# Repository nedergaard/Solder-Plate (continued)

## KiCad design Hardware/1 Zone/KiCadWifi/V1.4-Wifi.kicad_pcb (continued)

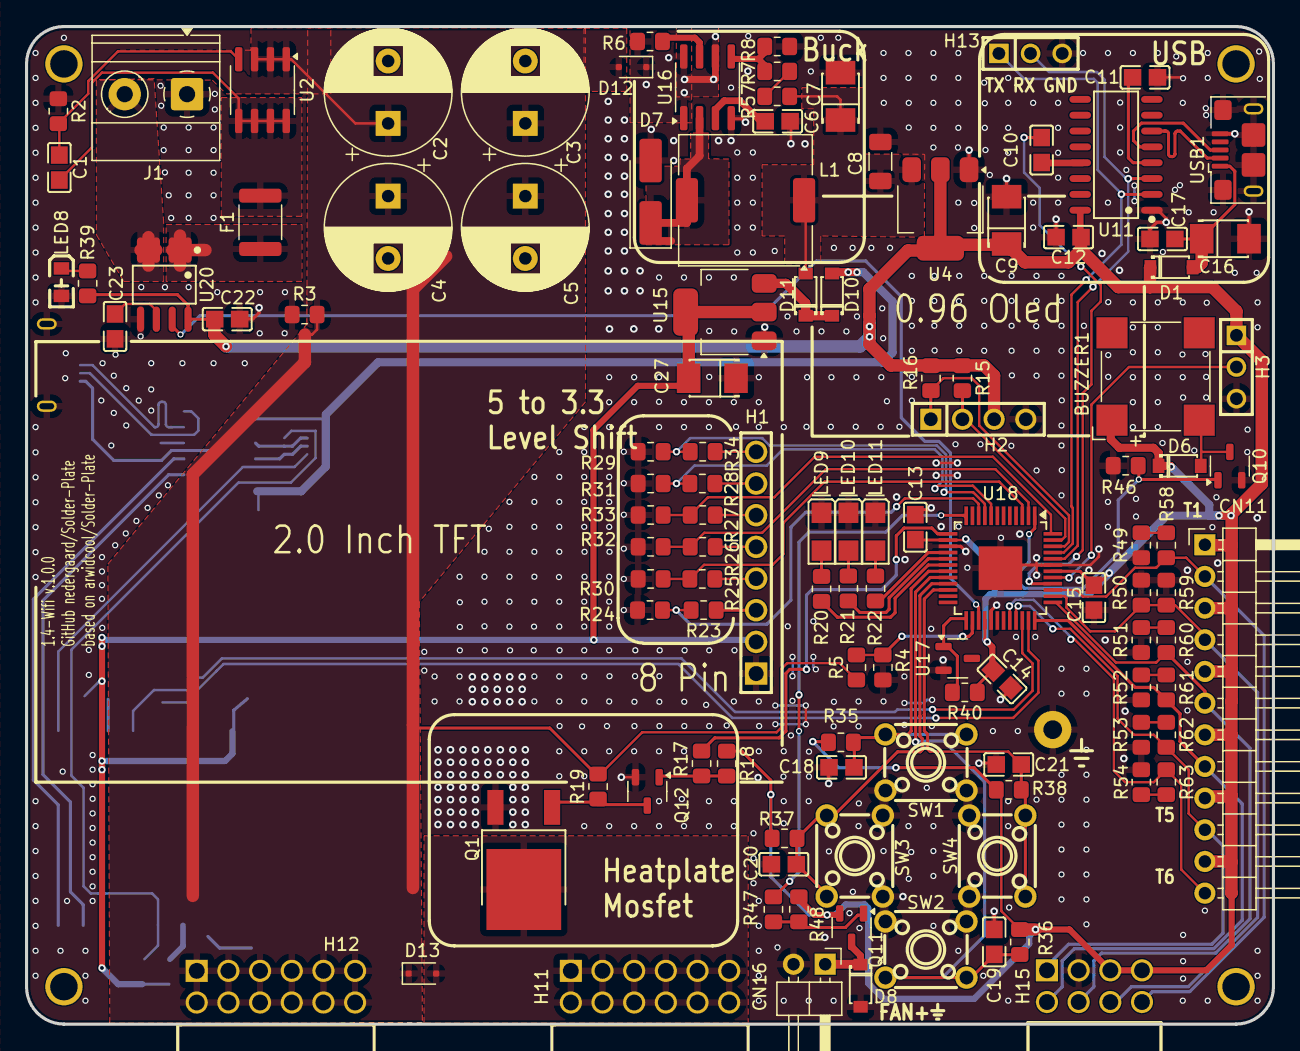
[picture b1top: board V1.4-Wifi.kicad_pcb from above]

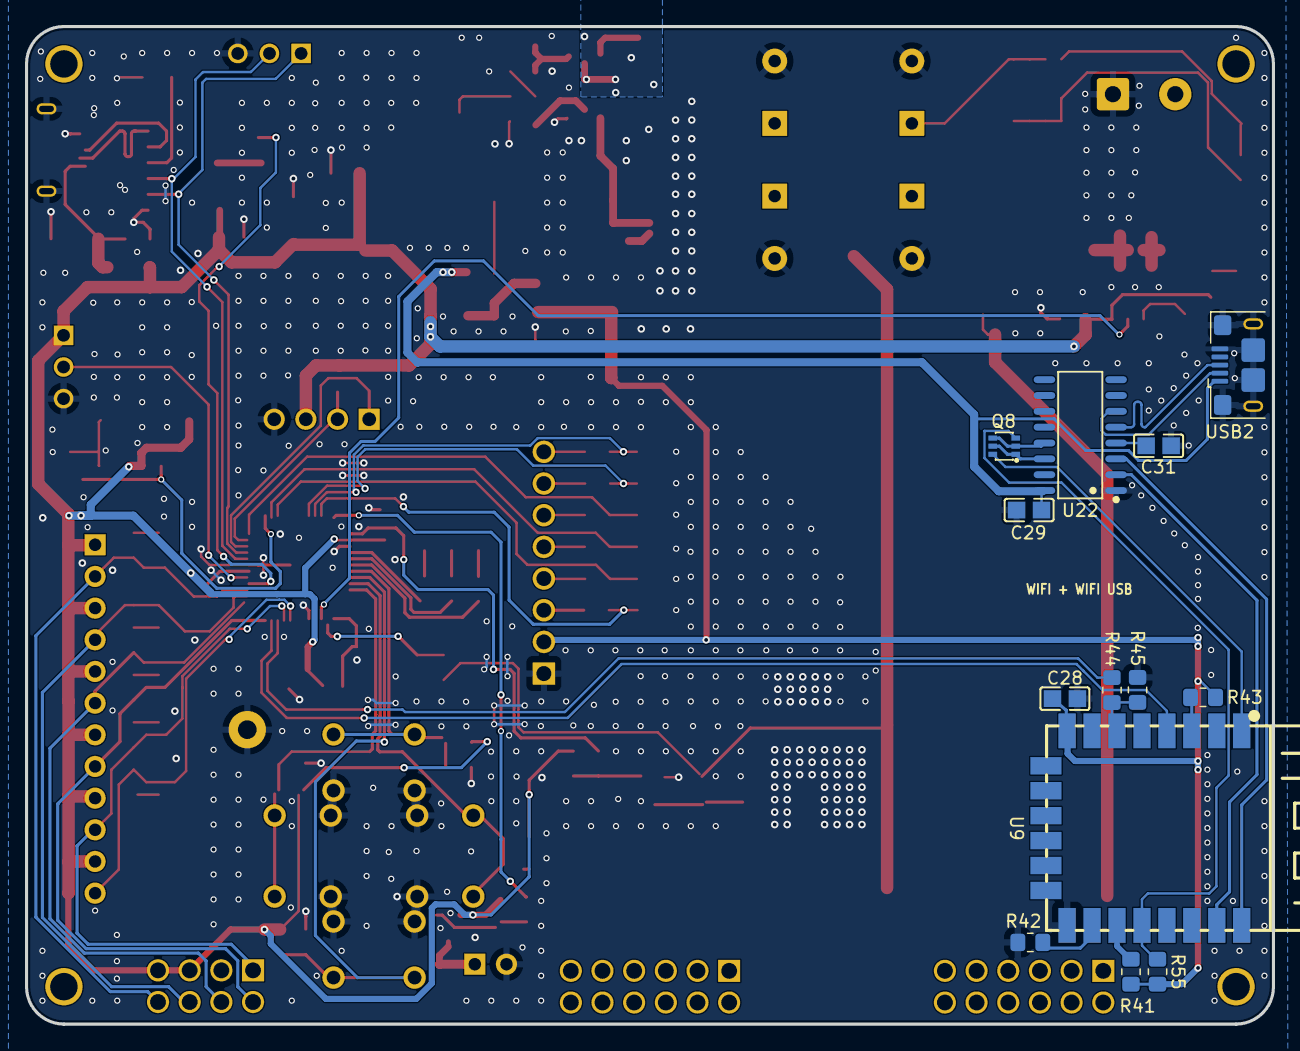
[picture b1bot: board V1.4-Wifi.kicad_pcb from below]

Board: 2 copper layers, 100.0 x 80.0 mm, 128 parts (13 on the bottom side), 90 nets.

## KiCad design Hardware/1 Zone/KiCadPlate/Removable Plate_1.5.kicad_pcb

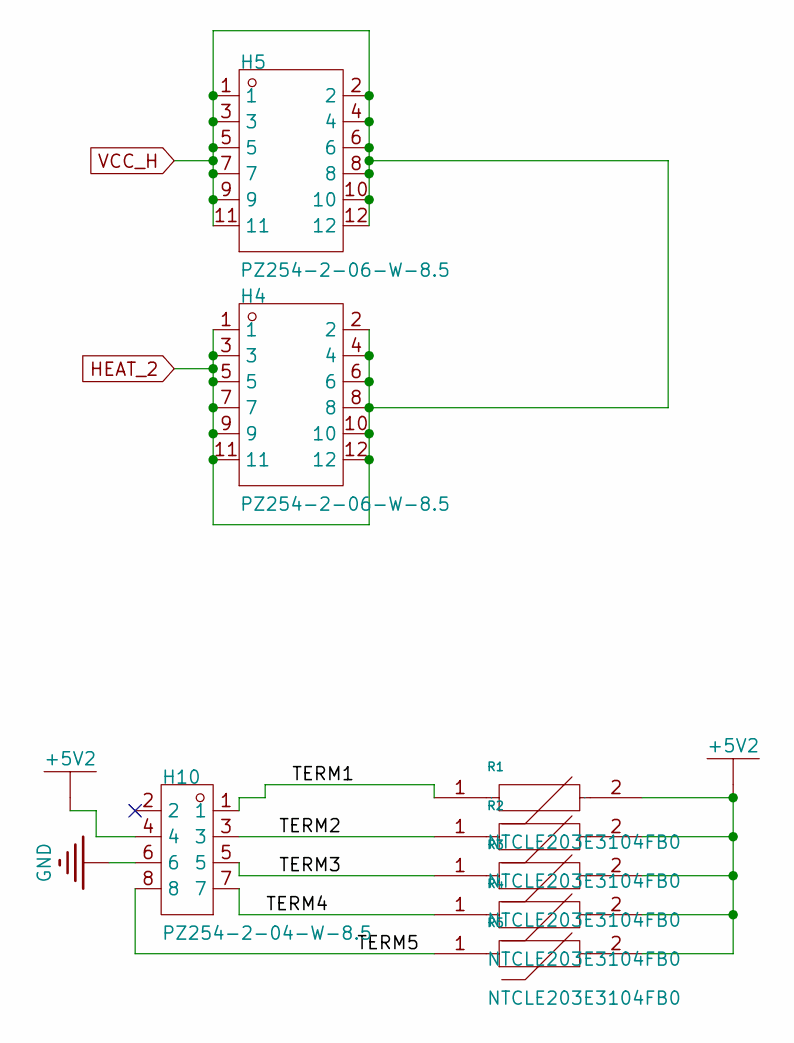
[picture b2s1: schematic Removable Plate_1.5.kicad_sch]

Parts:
H4, H5: PZ254-2-06-W-8.5; HDR-TH_12P-P2.54-H-M-R2-C6-S2.54-N; Manufacturer Part PZ254-2-06-W-8.5; LCSC Part Name 2.54mm2x6P弯插方针
H10: PZ254-2-04-W-8.5; HDR-TH_8P-P2.54-H-M-R2-C4-S2.54-N; Manufacturer Part PZ254-2-04-W-8.5; LCSC Part Name 2.54mm2x4P弯插方针
R1, R2, R3, R4, R5: NTCLE203E3104FB0; PinHeader_1x02_P2.54mm_Vertical; Manufacturer Part NTCLE203E3104FB0; LCSC Part Name 100kΩ电阻精度:±1%

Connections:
+5V2: H10.4, R1.2, R2.2, R3.2, R4.2, R5.2
/TERM1: H10.1, R1.1
/TERM2: H10.3, R2.1
/TERM3: H10.5, R3.1
/TERM4: H10.7, R4.1
/TERM5: H10.8, R5.1
GND: H10.6
HEAT_2: H4.1, H4.2, H4.3, H4.4, H4.5, H4.6, H4.7, H4.8, H4.9, H4.10, H4.11, H4.12, H5.1, H5.2, H5.3, H5.4, H5.5, H5.6, H5.7, H5.8, H5.9, H5.10, H5.11, H5.12

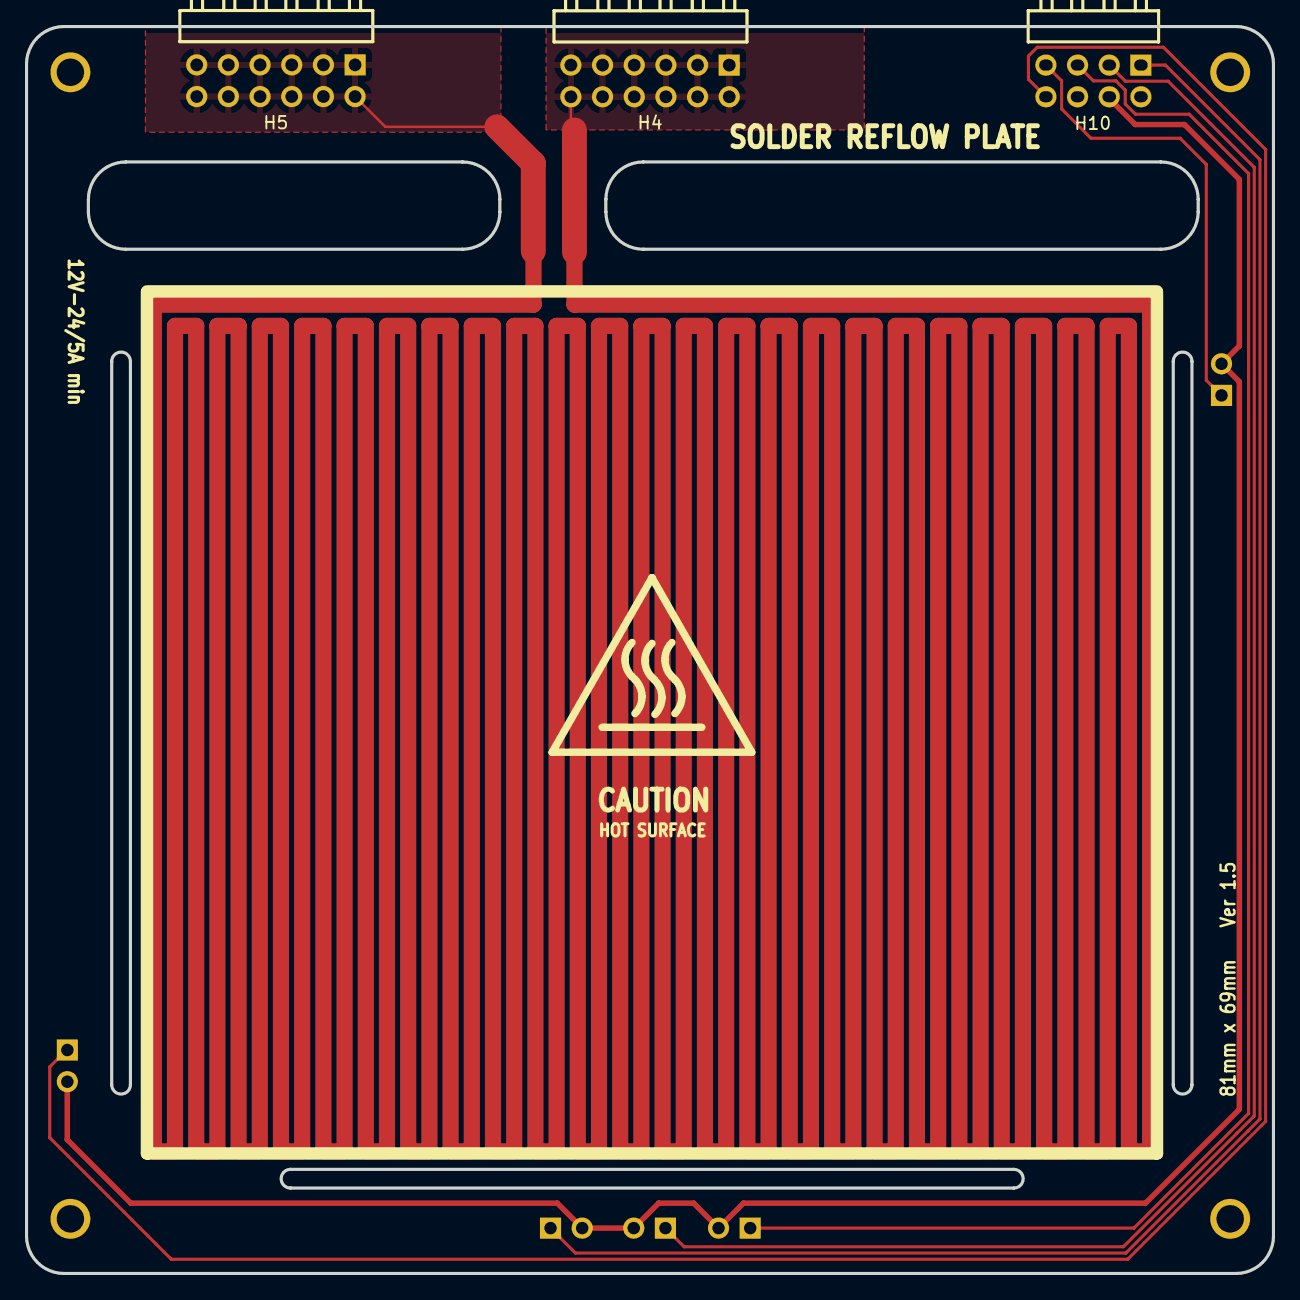
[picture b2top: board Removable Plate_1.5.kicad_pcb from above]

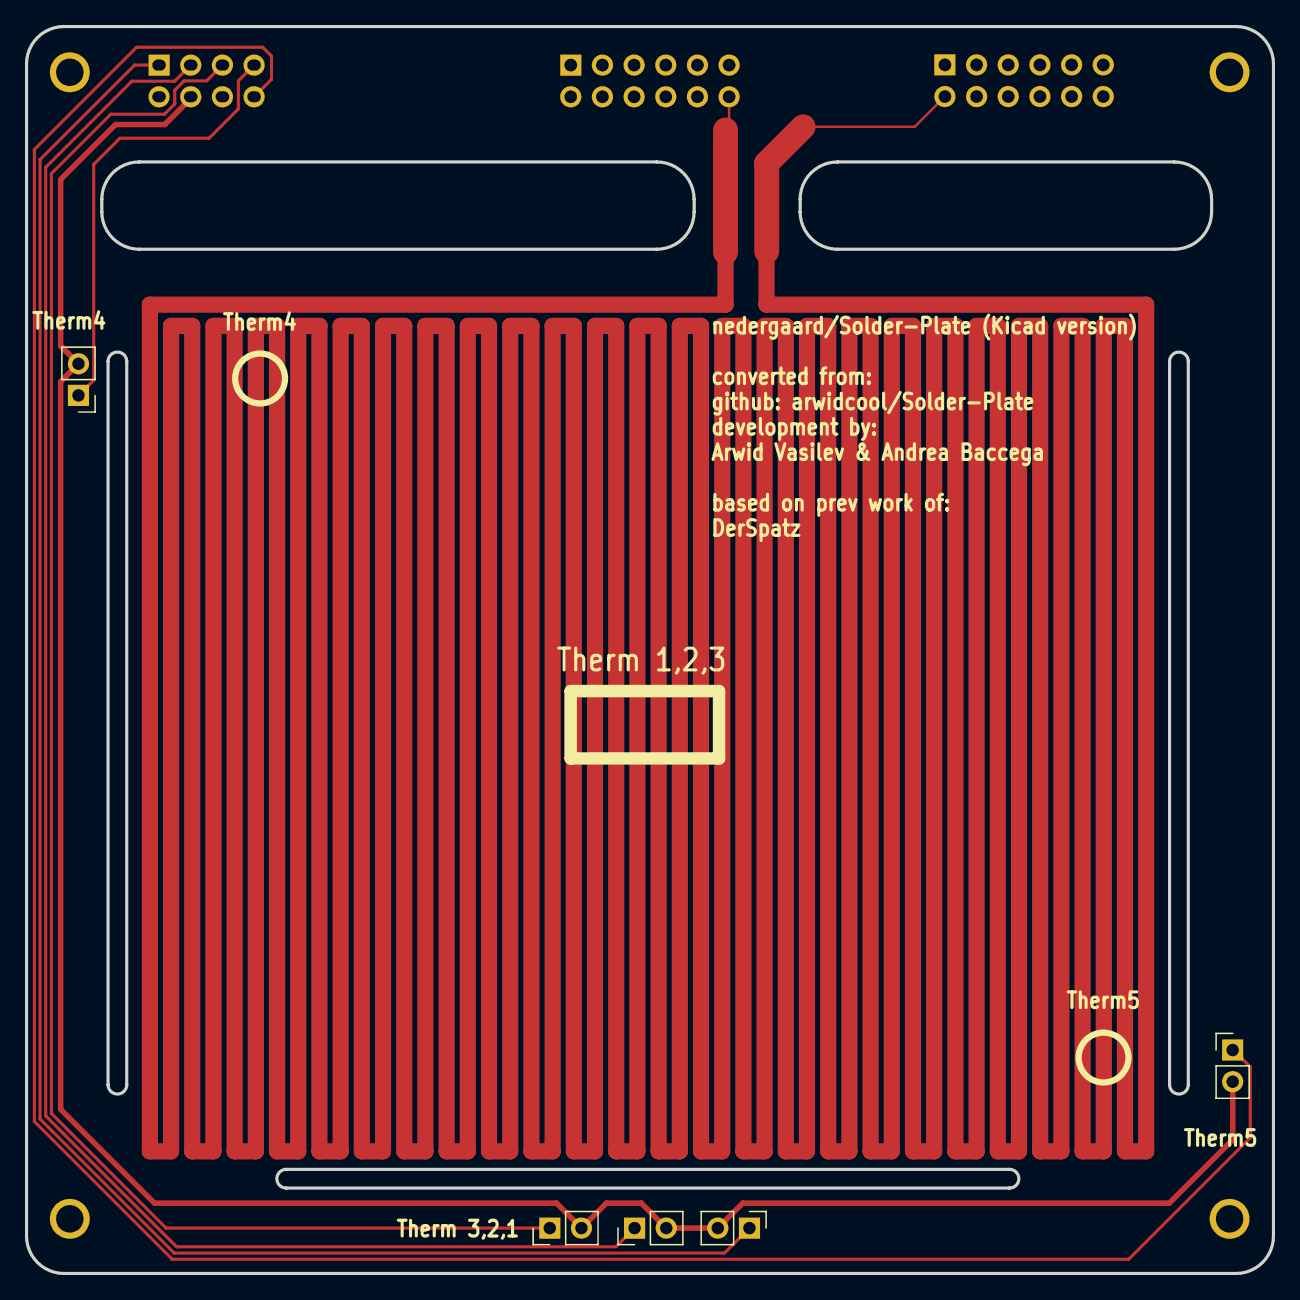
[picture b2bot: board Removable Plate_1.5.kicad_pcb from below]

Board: 2 copper layers, 100.0 x 100.0 mm, 8 parts (5 on the bottom side), 7 nets.

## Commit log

2025-03-30 Added readme note to contribute to the original repo
2025-04-12 Disable conversion of line endings by git
2025-04-12 Git ignore KiCad local files
2025-04-12 Added KiCad 9 project for V1.4-Wifi hardware
2025-04-12 Marked no-connect as such, except 1
2025-04-13 Added custom footprint library
2025-04-13 Replaced part C7, C9, C16 from TC212B107M010B to KEMET T491B107M010AT
2025-04-13 Git ignore KiCad folders with manual backup zips
2025-04-13 Replaced XH2 connectors with pin headers (CN11-CN16). Added Thermistor 1 to connector. Update 5V symbols with +5V value to inform KiCad about net connection.
2025-04-13 Replaced part D1, D6-D8, D10-D11 from MBR0520 to B0520LW-7-F
2025-04-13 Removed unused footprints (C2-C5)
2025-04-13 Updated D12,D13 from B5819 to B5819WSL-TP and updated footprint
2025-04-13 Replaced part F1 from SMD025F-30 to 1812L050/30PR and updated footprint (1812, smaller)
2025-04-13 Replaced part L1 from CDRH74-220MT to VLS6045EX-220M-H and updated footprint. Moved CURRENT_READ trace slightly away from the inductor for noise reasons.
2025-04-14 Replaced part LED8-LED11
2025-04-14 Replaced part Q1 from AOD4184A to IPD90N04S403
2025-04-14 Replaced part Q10 from IRLML2502 to PJA3404A. Updated footprint.
2025-04-14 Replaced part Q11 from SI2300 to PJA3404A to simplify BOM. Updated footprint.
2025-04-14 Replaced part Q12 from S8050 to BC816-16VL. Updated footprint.
2025-04-16 Adjusted resistor value to assist picking correct part by pcb supplier
2025-04-17 Moved C2-C5 back in place
2025-04-17 Fixed R and C values manually looking at EasyEDA editor
2025-04-19 Updated MPN for updated C parts
2025-04-21 Replaced part U2 from AO4409 to DMPH4015SSSQ
2025-04-21 Slighty incresed fill areas connected to U2 for heat dissipation
2025-04-21 Replaced U4 from AMS1117-5.0 to LDI1117-05H
2025-04-21 Replaced U15 from AMS1117-3.3 to LD1117S33CTR
2025-04-27 Upgraded L1 (MSS1048-104MLC) and D7 (SK34SMA-3G). Layout changes to accomodate larger footprints.
2025-04-27 Rotated D7 to shorten GND path. Added VIN fill on bu below U16 for heat dissipation.
2025-04-27 Replaced U17 custom footprint with standard
2025-04-27 Replaced U18 AtMega footprint with center pad. A bit of rerouting and GND stitching for EMC improvements (shrink GND loops)
2025-04-28 Replaced USB1, USB2 to 10118193-0001LF
2025-04-28 Replace Buzzer1 with CMT-8504-100-SMT-TR
2025-04-28 Cleaned pup symbol table
2025-04-28 Reroute (minor), moved via and silkscreen apart, in USB area
2025-04-28 Changed R1,R2 and all 10K resistors to 0805. Fixed comment for C28.
2025-04-28 Changed all 4K7 resistors to 0805.
2025-04-28 Changed all 1K resistors to 0805. Moved R39 and LED8 a little.
2025-04-28 Changed R6-R8,R40-R44,R50,R55 to 0805. Rerouted E_RESET,ESP_BOOT,3.3V. Fixed value of R39,R44
2025-04-29 Changed R45,R47,R49-R54 to 0805. Updated value for R41,R55.
2025-04-29 Changed via drill to 0.300mm. Default net clearance to 0.1mm. Border to edge 0.3mm. Fixed PCB DRC errors. 2 ignored.
2025-04-29 Removed bom field MPN. Renamed Manufacturer Part to mpn.
2025-04-29 Updated R50 to 2K, R6 to 0.33.
2025-04-29 Changed R20,22,39 based on LED calculations
2025-04-29 Changed C8 to 1205
2025-04-30 Added R56 (4K7) and changed R3 to 4K7, to dissipate power safely (slower discharge of caps).
2025-04-30 Added R57, changed R7,R8 to make ref voltage divider use E12. Fixed text with formula for Vout in 7.5V Step Down Converter.
2025-04-30 Removed R9-R14 pots for thermistor. Added R58-R63 to get good resistor matches for recommended values.
2025-04-30 Changed R44 to 2K2, R45 to 3K3 to get a safe conversion from 5V to 3V3 logic (ATMEGA to ESP12)
2025-04-30 Filled values for various header parts
2025-05-05 Replaced C2-C5 and LED10 (+R21) due to availability.
2025-05-10 Tidied up schematics
2025-05-10 Replaced Power Jack with screw terminals. Repurposed R3 to bleeder resistor. R1, R53 removed.
2025-05-17 Renamed MOSTFET to GATE_PIN, to align better with schematics.
2025-05-17 Rerouting for tighter return paths for MOSI and SCK. Moved R4,R5 to avoid cutting return path. Renamed LCD_RST, CD, DC to TFT_RST, TFT_CS, TFT_CS to better align with code.
2025-05-17 Removed H10 7pin header for TFT, for EMC reasons.
2025-05-17 UDPI net shortened and added tight return path.
2025-05-18 I2C_SCL, I2C_SDA return paths tightened
2025-05-18 RXD, TXD return paths tightened
2025-05-18 MEGA_TX, MEGA_RX return paths tightened up
2025-05-20 GATE, FAN_CTRL return paths tightened
2025-05-20 Renamed TFT_LED, TFT_SI_OUT, TFT_SCK_OUT to LCD_* for consistency
2025-05-20 E_TX, R_TX return paths tightened
2025-05-21 Cleaning. Simplified segmented traces.
2025-05-24 Moved D8 for EMC reasons. Refactored Fan ctrl schematic. BOM details corrected.
2025-05-24 BOM detailes corrected
2025-05-24 Changed C27 to T491B107M010AT due to availablility
2025-05-24 Moved C27 to avoid disrupting D+_E, D-_E return paths
2025-05-25 Rerouted D+,D-,E_D+,E_D- differential pairs to reduce gap between them. Renamed D+_E, D-_E for KiCad reasons.
2025-05-30 Refactor. Visual improvements to PCB layout.
2025-05-31 Added Kicad 9 project for Removable Plate v1.5
2025-06-05 Refactor. Visual improvements to PCB layout
2025-06-05 Rerouted D+,D-,E_D+,E_D- differential pairs, moving tuning part closer to where the length mismatch occurs
